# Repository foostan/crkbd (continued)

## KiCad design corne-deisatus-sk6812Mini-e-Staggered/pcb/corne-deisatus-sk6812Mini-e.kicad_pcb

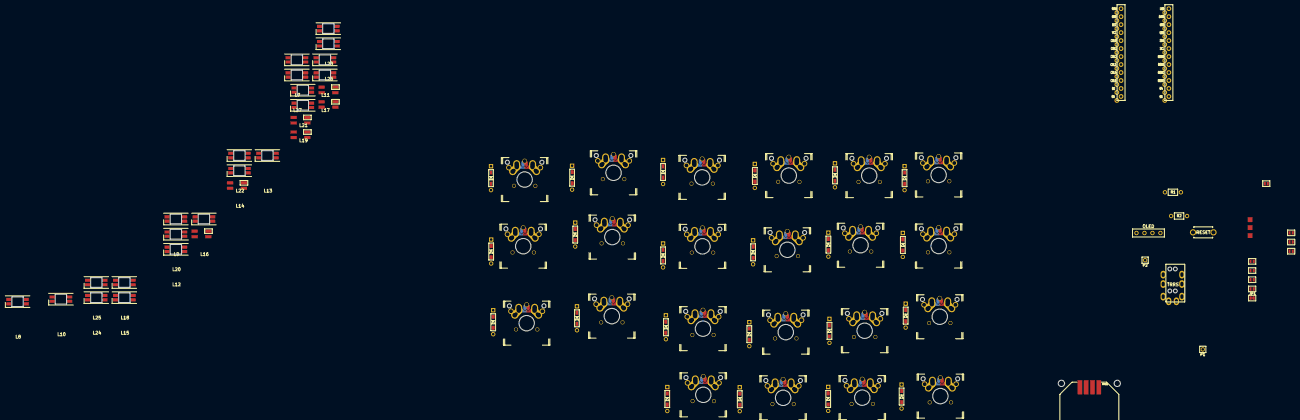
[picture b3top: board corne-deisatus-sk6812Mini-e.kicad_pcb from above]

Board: 2 copper layers, 90 parts (0 on the bottom side), 73 nets, no tracks yet.

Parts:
D1, D2, D3, D4, D5, D6, D7, D8, D9, D10, D11, D12, D13, D14, D15, D16, D17, D18, D19, D20, D21, D22: D; D3_TH_SMD
J1: MJ-4PP-9
J2: OLED
J3: LED; StripLED_rev
JP1: JP
JP2, JP3, JP4, JP5, JP6, JP7, JP8, JP9: Jumper
L1, L2, L3, L4, L5, L6: SK6812MINI; SK6812MINI_underglow_rev
L7, L8, L9, L10, L11, L12, L13, L14, L15, L16, L17, L18, L19, L20, L21, L22, L23, L24, L25, L26, L27: SK6812MINI-E; YS-SK6812MINI-E
P1, P2: i2c-pin; 1pin_conn
R1, R2: R
RSW1: SW_PUSH; ResetSW
RV11: JOYSTICK-PSP1000; JOYSTICK-PSP1000-reverse
SW1, SW2, SW3, SW4, SW5, SW6, SW7, SW8, SW9, SW10, SW11, SW12, SW13, SW14, SW15, SW16, SW17, SW18, SW19, SW21, SW22: SW_PUSH; MX-ALPS-Choc-X-straight-crane2
SW20: SW_PUSH; MX-ALPS-Choc-X-straight-crane2-u1.25
U1: ProMicro; ProMicro_v2

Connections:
AnalogX: RV11.1, U1.12
AnalogY: RV11.3, U1.11
GND: J1.C, J3.1, JP2.1, JP9.1, L1.2, L2.2, L3.2, L4.2, L5.2, L6.2, L7.3, L8.3, L9.3, L10.3, L11.3, L12.3, L13.3, L14.3, L15.3, L16.3, L17.3, L18.3, L19.3, L20.3, L21.3, L22.3, L23.3, L24.3, L25.3, L26.3, L27.3, RSW1.2, RV11.2, U1.3, U1.4, U1.23
LED: J3.2, L3.3, U1.1
unnamed: D1.2, SW1.2
unnamed: D2.2, SW2.2
unnamed: D3.2, SW3.2
unnamed: D4.2, SW4.2
unnamed: D5.2, SW5.2
unnamed: D6.2, SW6.2
unnamed: D7.2, SW7.2
unnamed: D8.2, SW8.2
unnamed: D9.2, SW9.2
unnamed: D10.2, SW10.2
unnamed: D11.2, SW11.2
unnamed: D12.2, SW12.2
unnamed: D13.2, SW13.2
unnamed: D14.2, SW14.2
unnamed: D15.2, SW15.2
unnamed: D16.2, SW16.2
unnamed: D17.2, SW17.2
unnamed: D18.2, SW18.2
unnamed: D19.2, SW20.2
unnamed: D20.2, SW21.2
unnamed: D21.2, SW22.2
unnamed: D22.2, SW19.2
unnamed: J1.A, P1.1
unnamed: J1.B, JP1.2, P2.1
unnamed: J2.1, JP5.2, JP9.2
unnamed: J2.2, JP4.2, JP8.2
unnamed: J2.3, JP3.2, JP7.2
unnamed: J2.4, JP2.2, JP6.2
unnamed: L1.1, L4.3
unnamed: L1.3, L2.1
unnamed: L2.3, L3.1
unnamed: L4.1, L5.3
unnamed: L5.1, L6.3
unnamed: L7.4, L8.2
unnamed: L9.4, L10.2
unnamed: L10.4, L16.2
unnamed: L11.2, L17.4
unnamed: L11.4, L12.2
unnamed: L12.4, L18.2
unnamed: L13.2, L19.4
unnamed: L7.2, L13.4
unnamed: L8.4, L14.2
unnamed: L14.4, L20.2
unnamed: L15.2, L21.4
unnamed: L9.2, L15.4
unnamed: L16.4, L22.2
unnamed: L17.2, L23.4
unnamed: L18.4, L24.2
unnamed: L20.4, L21.2
unnamed: L22.4, L25.2
unnamed: L23.2, L26.4
unnamed: L24.4, L27.2
unnamed: L25.4, L26.2
unnamed: L6.1, L27.4
SCL: JP4.1, JP7.1, R2.2, U1.6
SDA: JP5.1, JP6.1, R1.2, U1.5
VCC: J1.D, J3.3, JP3.1, JP8.1, L1.4, L2.4, L3.4, L4.4, L5.4, L6.4, L7.1, L8.1, L9.1, L10.1, L11.1, L12.1, L13.1, L14.1, L15.1, L16.1, L17.1, L18.1, L19.1, L20.1, L21.1, L22.1, L23.1, L24.1, L25.1, L26.1, L27.1, R1.1, R2.1, RV11.4, U1.21
col0: SW1.1, SW7.1, SW13.1, U1.20
col1: SW2.1, SW8.1, SW14.1, U1.19
col2: SW3.1, SW9.1, SW15.1, SW19.1, U1.18
col3: SW4.1, SW10.1, SW16.1, SW20.1, U1.17
col4: SW5.1, SW11.1, SW17.1, SW21.1, U1.16
col5: SW6.1, SW12.1, SW18.1, SW22.1, U1.15
data: JP1.1, U1.2
reset: RSW1.1, U1.22
row0: D1.1, D2.1, D3.1, D4.1, D5.1, D6.1, U1.7
row1: D7.1, D8.1, D9.1, D10.1, D11.1, D12.1, U1.8
row2: D13.1, D14.1, D15.1, D16.1, D17.1, D18.1, U1.9
row3: D19.1, D20.1, D21.1, D22.1, U1.10

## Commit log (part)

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2018-12-31 Remove unused file
2018-12-31 Fix acrylic plate size
2019-02-10 Update tent plate
2019-02-10 Rename acrylic_plates
2019-02-10 Update lines
2019-02-15 Add 1side
2019-02-19 Add tilting tenting doc
2019-02-19 Update light
2019-02-22 Update buildguide_tilting_tenting_plate_jp.md
    非対応分を明確に修正
2019-03-30 Update pretties
2019-04-20 Update footprints
2019-07-14 outline-fix
2019-09-30 added a 5 col layout, not tested
2019-10-02 Update LICENSE
2019-10-02 Update acrylic_plates
2019-10-02 Add plate for mini
2019-10-10 Improved LED soldering section of english build guide.
    Adds some extra info on how to orient the LEDs, how you can go about soldering
    them and a warning that LEDs need to be turned on in the default firmware to
    actually light up.
2019-10-10 Added clearer ProMicro orientation instructions to the english build guide.
2019-10-10 Added info on how to turn LEDs on to the firmware section of the english build guide.
2019-10-10 Added a troubleshoot section to the english build guide.
2019-11-20 Update configs
2019-11-26 Add build-guide for corne-light
2019-11-26 Add corne-light photos in README.md
2019-12-13 fixed typo
2020-02-11 Add cherry+ top-middle plate
2020-02-11 Move case/acrylic_plate to plates
2020-04-13 Add kailh low profiile
2020-05-19 Add tenting mini crkbrd version
2020-06-26 gitignore: simplify _gerber_ dir exclusion
    gitignore globs are not repo-global by default.
    They are so only with an explicit `/` in front.
    Also, all files below an ignored directory
    are ignored as well.
2020-06-26 git ignore more files created by KiCAD (& co.)
2020-07-07 Improve Corne Chocolate EN build-guide (was google-translated)
    Apart form language, it also fixes formatting, so some links,
    images and code-blocks are now shown as they should.
2020-07-07 README: Adds links to the build guides
2020-08-01 [GitHub] Add release gerber files workflow
2020-08-04 Update cuts and footprints
2020-09-04 Move libralies to kicad-symbols dir
2020-09-04 Add kicad-packages3D
2020-09-04 Add git file
2020-09-04 Move kbd.pretty to kicad-footprints
2020-09-04 Fix cd dir
2020-09-04 Update the description of MJ-4PP-9
2020-09-04 Add sym-lib-table and checking it flow
2020-09-04 Update order of flow
2020-09-05 Fix syntax and order
2020-09-05 Ignore kicad-library-utils
2020-09-05 Update LICENSE to be included foostan only
2020-09-05 Add README.md
2020-09-05 Update pcb plates
2020-09-05 Update acrylic plates
2020-09-05 Cleanup
2020-09-05 Add git-submodule
2020-09-05 Add Makefile
2020-09-27 Update the build guide for corne cherry v3
2020-09-27 Update messages
2020-09-27 Add kicad-packages3D models
2020-09-27 Update sch
2020-09-27 Remove logo
2020-10-01 Fix hole size
2020-10-02 Fix tilting doc path
2020-10-13 Update lib path
2020-10-13 Move to current docs to v1
2020-11-03 Update board
2020-11-03 Add alps compatible switche footprint
2020-11-03 Add try mount plate
2020-11-03 Update firmware documentations
2020-11-03 Update the firmware section of each keyboard
2020-11-03 Update links
2020-11-03 Add svg files for latest Corne Cherry
2020-11-03 Add new footprint for thread
2020-11-03 Update layer options
2020-11-03 Update submodules
2020-11-12 Add new symbol for light
2020-11-13 Create or Update plate data for corne-light
2020-11-13 Update action
2020-11-13 Update corne light plates
2020-11-30 Fix spacer length and screw length
2020-12-08 Update the link of firmware to latest
2021-01-20 added libraries to folder, changes footprint associations
2021-01-20 reverted corne classic to original, made new folder
2021-01-20 fixed all edges
2021-01-21 Turn Choc key socket footprint 180 degree.
2021-01-21 adding tracks
2021-01-22 mostly done
2021-01-22 all tracks done
2021-01-23 Update buildguide_en.md typo fix
    Minor cleanup commit fixing a typo wholes -> holes) in the English build guide.
2021-01-27 rebuilt gerbers, changed file names
2021-02-03 made led reversable
2021-02-03 updated nets
2021-02-03 Updated PCB for new pins
2021-02-03 re adding tracks
2021-02-03 removed unneeded cuts, updated gerber
2021-02-15 added footprint
2021-04-17 Improves MarkDown standards conformity
2021-04-17 Converts pseudo-headers into real ones
2021-04-17 README: Minor white-space cleanup
2021-04-29 Correct minor typo in buildguide_en.md
2021-05-15 Unifies table headers
2021-05-15 Add all missing English translations of MD documents
    ... using Google translate + manual MD syntax fixing
2021-05-15 Fixes paths to 3 images
2021-05-15 Unifies instructions a bit, and improves grammar and wording
2021-06-29 edited .plates/common/*.svg to make them working with inkscape
2021-06-29 added more .svg files
2021-08-24 Fix the outlines of classic
2021-09-24 joined nodes of plate's outline path
2021-11-07 Update README.md
    https://forum.kicad.info/t/warning-avoid-all-links-to-kicad-pcb-org-use-kicad-org/31521
2021-12-26 Update gitignore for kicad6
2022-02-16 Adds SPDX license info (REUSE compliance)
2022-02-16 README: Adds the REUSE badge
2022-03-09 Update KiCad EDA links
2022-03-16 initial
2022-03-29 update firmware reference + more build guide things
2022-04-07 Fix the PCB outline of chocolate
2022-06-04 rename dirs
2022-07-18 first workflow
2022-12-11 Finished wiring
2022-12-11 Fixed unconnected components
2022-12-11 Fixed proper sizing and rerouted
2022-12-12 Added keebio symbols and footprints
2023-01-04 cherry
2023-01-04 chocolate
2023-01-04 light
2023-01-04 plates
2023-06-24 Fix wrong path in Makefile
2023-06-24 Use project relative paths to 3d models
2023-06-24 Clean up old footprints
2023-07-14 Update hotswap switches
2023-07-14 Squashed 'corne-chocolate/pcb/kbd/' content from commit 9646f49
    git-subtree-dir: corne-chocolate/pcb/kbd
    git-subtree-split: 9646f492fff643907c0444ce62bd6eb57c50b4bc
2023-07-14 Squashed 'corne-classic/pcb/kbd/' content from commit 9646f49
    git-subtree-dir: corne-classic/pcb/kbd
    git-subtree-split: 9646f492fff643907c0444ce62bd6eb57c50b4bc
2023-07-14 Update Makefile
2023-07-14 Squashed 'pcb/kbd/' content from commit 00201b6
    git-subtree-dir: pcb/kbd
    git-subtree-split: 00201b6ef2bc9ab2800b878e3095ed44aeda937a
2023-09-23 Add rotary encoder
2023-09-23 Squashed 'pcb/kbd/' changes from 00201b6..da6b024
    da6b024 Delete unused footprint
    00d6f0c Add rotary encoder
    git-subtree-dir: pcb/kbd
    git-subtree-split: da6b024aa2958eb2353cbe3a6dc57dd9080cd656
2023-09-23 Add the 3D model of TYPE-C-31-M-13C
2023-09-23 Add assigns
2023-09-23 Add ST-0277D00-052-142
2023-09-23 Squashed 'pcb/kbd/' changes from 9711222..8cc619e
    8cc619e Add ST-0277D00-052-142
    git-subtree-dir: pcb/kbd
    git-subtree-split: 8cc619ee7e99e89baa22aea76c0537ca33a052b2
2023-09-23 Squashed 'pcb/kbd/' changes from 8cc619e..b354fc0
    b354fc0 Fix pin number
    git-subtree-dir: pcb/kbd
    git-subtree-split: b354fc02b871ef1c24bf8d03fd3ff7a7ee5d9545
2023-09-24 Update CrtYd
2023-09-26 Add smd switch
2023-09-26 Squashed 'pcb/kbd/' changes from ab94e05..57d0a68
    57d0a68 Add smd switch
    git-subtree-dir: pcb/kbd
    git-subtree-split: 57d0a6803ee76549f20bb3601fda7103a485a96c
2023-09-27 Set each part
2023-09-27 Squashed 'pcb/kbd/' changes from 57d0a68..3a51036
    3a51036 Add mergin area
    git-subtree-dir: pcb/kbd
    git-subtree-split: 3a51036ff6c0d2511e5c2c71c14746ac71c4f29a
2023-09-30 Add lines
2023-09-30 Squashed 'pcb/kbd/' changes from 3a51036..1e68599
    1e68599 Fix positions
    git-subtree-dir: pcb/kbd
    git-subtree-split: 1e6859946104ea7de8c202f10c3c8eddc143db14
2023-09-30 Squashed 'pcb/kbd/' changes from 1e68599..a1a5b18
    a1a5b18 Fix pad positions
    git-subtree-dir: pcb/kbd
    git-subtree-split: a1a5b18d8f7a5969aae8d740563d380ecc7f5430
2023-09-30 Squashed 'pcb/kbd/' changes from a1a5b18..a2fdf46
    a2fdf46 Update lines
    git-subtree-dir: pcb/kbd
    git-subtree-split: a2fdf4689355d9eec99c518ad68d304fb75dfe0b
2023-09-30 Update positions
2023-09-30 Squashed 'pcb/kbd/' changes from a2fdf46..148d932
    148d932 Fix footprint type
    git-subtree-dir: pcb/kbd
    git-subtree-split: 148d9328eeec21db74b07cd60d3d3c1f7de27ad5
2023-09-30 Fix some errors
2023-09-30 Squashed 'pcb/kbd/' changes from 148d932..043d4bd
    043d4bd Update pad positions
    git-subtree-dir: pcb/kbd
    git-subtree-split: 043d4bd18d2ea93479190ac4e489e7355e124a9e
2023-10-01 Finish left hand
2023-10-04 Fix attr
2023-10-04 Squashed 'pcb/kbd/' changes from affd835..fe5de30
    fe5de30 Add parts area
    0f5ea3b Fix attr
    git-subtree-dir: pcb/kbd
    git-subtree-split: fe5de303769462056fd0c544a8fa1ca451ca1390
2023-10-05 Fix the `nerdyscout/kicad-exports` schema args
2023-10-05 Upgade `nerdyscout/kicad-exports` to v2.2
2023-10-05 Upgade `nerdyscout/kicad-exports` to v2.3
2023-10-05 Switch `INTI-CMNB/KiBot` to v2_k6
2023-10-07 Convert symbol lib new format
2023-10-07 Fix footprints
2023-10-07 Squashed 'pcb/kbd/' changes from 41976fe..7d74185
    7d74185 Fix footprints
    git-subtree-dir: pcb/kbd
    git-subtree-split: 7d741855d240a547847f258a2e0e18a2b7158eb2
2023-10-07 Squashed 'pcb/kbd/' changes from 7d74185..53b71bc
    53b71bc Fix ref size
    git-subtree-dir: pcb/kbd
    git-subtree-split: 53b71bc4bfd7a9b551b3a8283b9c1c7a54f56529
2023-10-16 Add new plate data for new version
2023-10-16 Fix position
2023-10-16 Squashed 'pcb/kbd/' changes from 53b71bc..b377b10
    b377b10 Fix position
    git-subtree-dir: pcb/kbd
    git-subtree-split: b377b107aabd5b0266aa88b4489bf3631e9000c8
2023-10-18 Squashed 'pcb/kbd/' changes from b377b10..7fb7779
    7fb7779 Update choc socket
    git-subtree-dir: pcb/kbd
    git-subtree-split: 7fb777965bbec1add41354a3065d91e341473b00
2023-10-18 Update directory trees
2023-10-18 Update filenames
2023-10-18 Add chocolate
2023-10-18 Remove kbd dir
2023-10-18 Squashed 'pcb/common/kbd/' changes from 3a70a10..b6de4ec
    b6de4ec Add choc with rotary encoder
    git-subtree-dir: pcb/common/kbd
    git-subtree-split: b6de4ec0de6193a4bb4ef3e53e3efbe071e91a35
2023-10-18 Update pad name
2023-10-21 Update ref positions
2023-10-21 Squashed 'pcb/common/kbd/' changes from 805f605..192148e
    192148e Update ref positions
    git-subtree-dir: pcb/common/kbd
    git-subtree-split: 192148e2adc01683c1eab33d901bd1d5faa98ef2
2023-10-21 Squashed 'pcb/common/kbd/' changes from 192148e..b579ab6
    b579ab6 Adjust hole positions
    git-subtree-dir: pcb/common/kbd
    git-subtree-split: b579ab6b98a189e6aa56a4bafcde5954cc464b0a
2023-10-21 Adjust pad size
2023-10-21 Add teardrop
2023-10-21 Add ignore rule
2023-10-21 Fix output path
2023-11-06 Update footprints and sch
2023-11-06 Update jlcpcb files
2023-11-09 Fix pcb for jlcpcb policy
2023-11-11 Fix the thumb key for alps pcb plate
2023-11-11 Update pcbs fix to creatable
2023-11-12 Fix choc footprints
2023-11-12 fix gateron low profile
2023-11-12 Remove old files
2023-11-12 Add mx and alps footprint
2023-12-01 Update encoder pin
2023-12-03 move pcb files
2023-12-03 Add plates for v4
2023-12-03 Cleanup plate data
2023-12-15 Update order files
2023-12-15 Add production_files
2023-12-20 Fix fixed pin
2023-12-20 Update Pico-EZmate
2023-12-20 Squashed 'pcbs/common/kbd/' content from commit 43da0ca
    git-subtree-dir: pcbs/common/kbd
    git-subtree-split: 43da0ca3d5e3e0a628e7d64e4fce58097fee60bb
2023-12-20 Update choc v2 fixed pin
2024-01-26 Update choc silk
2024-02-12 Update docs and README
2024-02-23 Add case data
2024-02-27 add some oled cover files
2024-03-18 Remove old dir
2024-03-18 Fix for footprints for choc v2
2024-03-30 Fix for #223
2024-03-30 Update docs for v4
2024-04-19 Fix GND/VCC for mini version
2024-04-19 fix(links): correct english links
2024-04-24 Squashed 'pcbs/common/kbd/' changes from a74626e..c53bf51
    c53bf51 Fix pin name
    git-subtree-dir: pcbs/common/kbd
    git-subtree-split: c53bf519ed9e0a498869ab56d44385f89ec54b36
2024-05-06 Update docs
2024-06-09 Point dead links towards approriate version of firmware guide.
2024-10-03 Update buildguide_en.md, fixed typo
2024-11-15 Add a caution for EMI issue
2024-11-15 Change word caution to notice
2024-12-04 Generate production files
2024-12-17 Fix links in docs
2025-01-03 Add Corne Chocolate v4.1.1
2025-01-16 Update production files
